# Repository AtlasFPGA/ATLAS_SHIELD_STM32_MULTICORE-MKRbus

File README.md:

# ATLAS_SHIELD_STM32_MULTICORE-MKRbus

Primera versión del SHIELD MULTICORE STM32 MKRbus para I/O BOARD ATLAS, válido para todas las "I/O BOARD ATLAS" incluidas las "AKA NEPTUNE" se usan las hembras apiladas que normalmente se usan en los shield de arduino, para tener el multicore basado en STM32.

Group ATLAS in Telegram: https://t.me/INICIATIVAATLAS

Enlace cabezales hembra apilable:
https://es.aliexpress.com/item/4000059515638.html?pdp_npi=2%40dis%21EUR%211%2C16%E2%82%AC%211%2C06%E2%82%AC%21%21%21%21%21%40211b440316861499958111903e1e40%2110000000140557195%21btf&_t=pvid%3Af4806f4c-de05-4d23-908d-d920b1f8ac6d&afTraceInfo=4000059515638__pc__pcBridgePPC__xxxxxx__1686149996&spm=a2g0o.ppclist.product.mainProduct&gatewayAdapt=glo2esp

Las STM32 que se han usado son 2 modelos para el presente diseño SHIELD MULTICORE STM32:
Los modelos escogidos son el mismo que se usa en Muticore-II/UnAMIGA, pero en la versión de Victor Trucco, con una sóla SD en modo de acceso SPI 3V3, el modelo de tener microcontroladores o SBCs en el futuro es válido para futuros SHIELD MULTICORE que puedan aparecer con esta interconexión, al incorporar de esta forma la unión FPGA-SD-MICRO FPGA-SD-SBC, estamos en un puro derivado de MiST.

De hecho con el tiempo Victor trucco ha ido agregando más funcionalidad MiST a su versión con bluepill.

En este caso he colocado el mismo diseño que se ha usado en máquinas retro-fpga como,Multicore-II, UnAMIGA, Prototipos PEGASO & CENTAURO, Y las Retrofpga de más capacidad UnAMIGA-Reloaded y NePTUNO, puede que con eL añadido de VGA64 muchos cores de poca profundidad de color sean portables.

Como reservé 2 pines para un modo 4bit en SD, este se puede desarrollar con la BLACKPILL en la opción del chip más avanzado F411.
Hay por ahora tres modelos de BLACKPILL la BLACKPILL que posée SDIO de 1Bit, 4Bit u 8Bits -> SDIO es el STM32F411CEU6.

## Pineado bluepill

bluepill -> stm32f103c8t6

## Pineado BLACKPILL

BLACKPILL -> STM32F411CEU6

Nota: para posicionar correctamente los pines usamos mayúsculas para la BLACKPILL, y minúsculas para la bluepill.

## Dimensiones que compraten las STM32 usadas, a tener en cuenta de la bluepill y la BLACKPILL:

Avance del esquema multicore STM32:

# NOTA: PI_TX y PI_RX pasarán as ser lineas de selección del modelo heredado por el Multicore II de Victor trucco.
# La colocación de los STM32, son excluyentes.

Al usar la elevación de las hembras apilables, el montaje "I/O BOARD ATLAS y LA SHIELD STM32" nos dá más capas, me queda la duda de si en el bus MKR+PMOD se puedieran cortar los pines asociados en la parte macho de las hembras apilables apoderándose de las señales Reservadas hasta la fecha, R14_SD_DATA2 y P14_SD_DATA1 así como el AUDIO Estéreo y T12_LEFT_MKR R11_RIGHT_MKR, agregando 4 señales a esta opción de Multicore con bluepill, estoy planteado en el futuro agregar esta opción de robar pines a la FPGA incorporando 4 señales a un nuevo diseño opcional, lo que permite conectar desde Dispositivos SPI, I2S, 2 canales I2C, TX RX con gestión de bflujo -> Acceso a internet.

Si se guardan los pines cortados iniciando el diseño con el bluepill y en el futuro se desarrollara una opción viable con SDIO 4Bit en BLACKPILL, no es muy dificil volver a soldarlos donde se realizó el corte, o directamente no usar ese tipo de hembras apilables en el conector de audio -> poner simples hembras, y hacer lo mismo en DATA1 y DATA2, y ya se veria como colocar pads normalmente abiertos o cerrados para que una misma placa permita obtener pines de fpga.

Aunque gestionando la compra de placas bien podía costearse una placa para bluepill + 4Señales, y BLACHPILL modelo F411.

Mi opción inicial es que se puedan manejar más componentes hardware, y unificar la placa sin agregar más que conectores cortar o soldar pistas en los pad indicados.

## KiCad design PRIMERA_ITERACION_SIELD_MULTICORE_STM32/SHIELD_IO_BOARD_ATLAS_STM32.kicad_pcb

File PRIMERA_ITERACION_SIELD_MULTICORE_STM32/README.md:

# Documentos del proyecto kicad asociado al SHIELD MULTICORE STM32
STM32 Multicore STM32 for plug a bluepill or BLACKPILL with CYC1000 in MKR bus for sxpand the use of Atlas resources

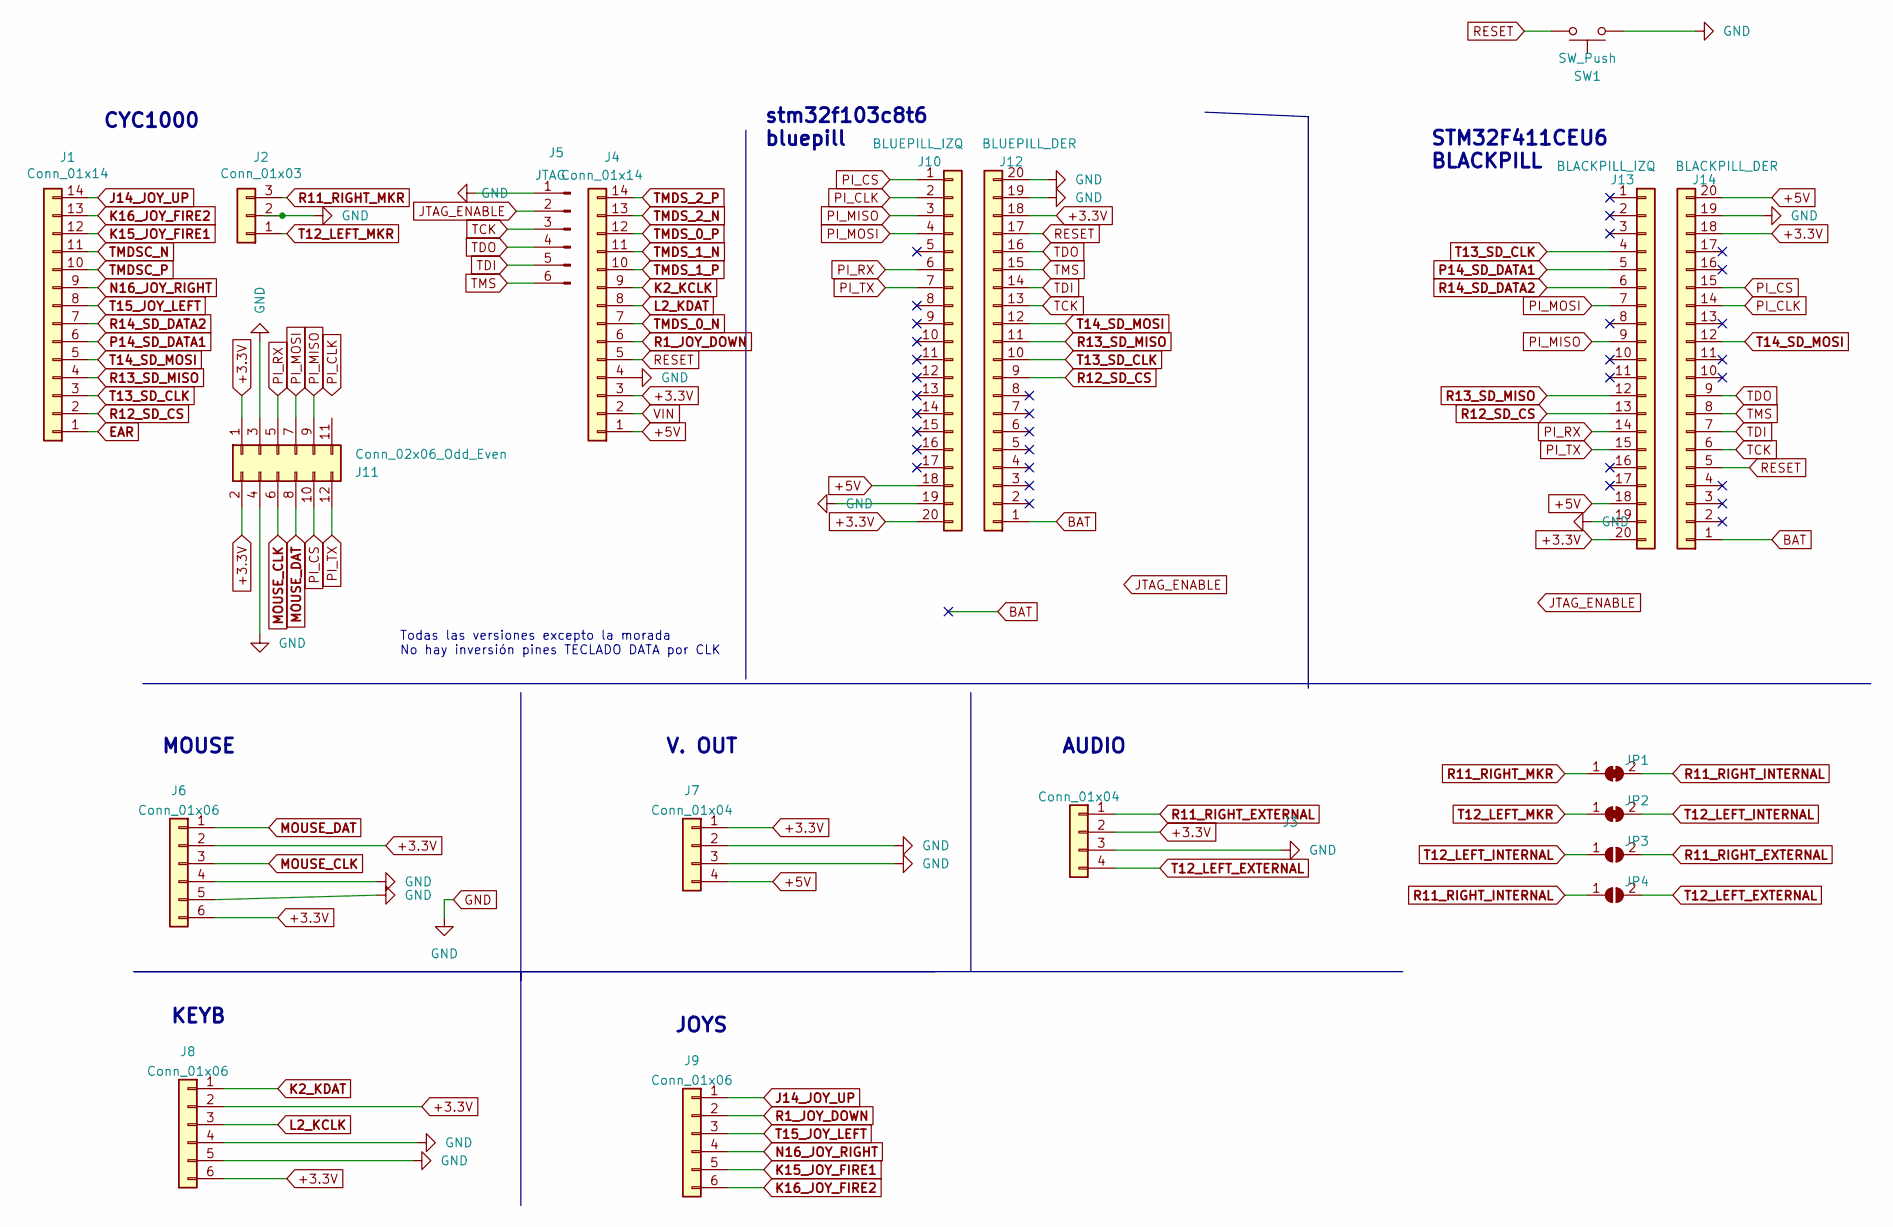
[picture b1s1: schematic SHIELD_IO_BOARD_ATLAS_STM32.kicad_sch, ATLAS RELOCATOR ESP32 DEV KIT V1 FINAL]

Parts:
J1, J4: Conn_01x14; PinHeader_1x14_P2.54mm_Vertical
J2: Conn_01x03; PinHeader_1x03_P2.54mm_Vertical
J3, J7: Conn_01x04; PinHeader_1x04_P2.54mm_Vertical
J5: JTAG; PinHeader_1x06_P2.54mm_Vertical
J6, J8, J9: Conn_01x06; PinHeader_1x06_P2.54mm_Vertical
J10: BLUEPILL_IZQ; PinHeader_1x20_P2.54mm_Vertical
J11: Conn_02x06_Odd_Even; PinHeader_2x06_P2.54mm_Vertical
J12: BLUEPILL_DER; PinHeader_1x20_P2.54mm_Vertical
J13: BLACKPILL_IZQ; PinHeader_1x20_P2.54mm_Vertical
J14: BLACKPILL_DER; PinHeader_1x20_P2.54mm_Vertical
JP1, JP2: SolderJumper_2_Bridged; SolderJumper-2_P1.3mm_Bridged2Bar_RoundedPad1.0x1.5mm
JP3, JP4: SolderJumper_2_Open; SolderJumper-2_P1.3mm_Open_RoundedPad1.0x1.5mm
SW1: SW_Push; SW_PUSH_6mm

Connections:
+3.3V: J3.2, J4.3, J6.2, J6.6, J7.1, J8.2, J8.6, J10.20, J11.1, J11.2, J12.18, J13.20, J14.18
+5V: J4.1, J7.4, J10.18, J13.18, J14.20
BAT: J12.1, J14.1
EAR: J1.1
GND: J2.2, J3.3, J4.4, J5.1, J6.4, J6.5, J7.2, J7.3, J8.4, J8.5, J10.19, J11.3, J11.4, J12.19, J12.20, J13.19, J14.19, SW1.2
J14_JOY_UP: J1.14, J9.1
JTAG_ENABLE: J5.2
K2_KCLK: J4.9
K2_KDAT: J8.1
K15_JOY_FIRE1: J1.12, J9.5
K16_JOY_FIRE2: J1.13, J9.6
L2_KCLK: J8.3
L2_KDAT: J4.8
MOUSE_CLK: J6.3, J11.6
MOUSE_DAT: J6.1, J11.8
N16_JOY_RIGHT: J1.9, J9.4
P14_SD_DATA1: J1.6, J13.5
PI_CLK: J10.2, J14.14
PI_CS: J10.1, J11.10, J14.15
PI_MISO: J10.3, J11.9, J13.9
PI_MOSI: J10.4, J11.7, J13.7
PI_RX: J10.6, J11.5, J13.14
PI_TX: J10.7, J11.12, J13.15
R1_JOY_DOWN: J4.6, J9.2
R11_RIGHT_EXTERNAL: J3.1, JP3.2 (B)
R11_RIGHT_INTERNAL: JP1.2 (B), JP4.1 (A)
R11_RIGHT_MKR: J2.3, JP1.1 (A)
R12_SD_CS: J1.2, J12.9, J13.13
R13_SD_MISO: J1.4, J12.11, J13.12
R14_SD_DATA2: J1.7, J13.6
RESET: J4.5, J12.17, J14.5, SW1.1
T12_LEFT_EXTERNAL: J3.4, JP4.2 (B)
T12_LEFT_INTERNAL: JP2.2 (B), JP3.1 (A)
T12_LEFT_MKR: J2.1, JP2.1 (A)
T13_SD_CLK: J1.3, J12.10, J13.4
T14_SD_MOSI: J1.5, J12.12, J14.12
T15_JOY_LEFT: J1.8, J9.3
TCK: J5.3, J12.13, J14.6
TDI: J5.5, J12.14, J14.7
TDO: J5.4, J12.16, J14.9
TMDSC_N: J1.11
TMDSC_P: J1.10
TMDS_0_N: J4.7
TMDS_0_P: J4.12
TMDS_1_N: J4.11
TMDS_1_P: J4.10
TMDS_2_N: J4.13
TMDS_2_P: J4.14
TMS: J5.6, J12.15, J14.8
VIN: J4.2

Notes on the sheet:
MOUSE
CYC1000
AUDIO
KEYB
JOYS
stm32f103c8t6 bluepill
Todas las versiones excepto la morada No hay inversión pines TECLADO DATA por CLK
STM32F411CEU6 BLACKPILL
V. OUT

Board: 2 copper layers, 19 parts (8 on the bottom side), 35 nets, no tracks yet.

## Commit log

2023-06-07 PRIMER README.md
    Multicore válido para BLACKPILL y BLUEPILL.
2023-06-07 Información Bluepill y blackpill
2023-06-07 Create Aclaración
    Inicio del proyecto en KICAD para el Multicore Shield STM32
2023-06-07 AÑADIDOS FICHEROS DE KICAD, MODELO UNA ÚNICA SD PARA ATLAS
2023-06-07 Imágenes de los STM32 usados, README.md
2023-06-07 Esquema común para desarrollo de un multicore STM32
    BLACKPILL -> SIO 4BIT
    bluepill -> SPI
2023-06-07 Agregada imagen del Diagrama multicore para bluepill y BLACKPILL README.md
2023-06-07 Añadir foto de Hembras apilables
2023-06-07 Agregar información sobre donde comprar las hembras apilables README.md
2023-06-07 Añadir información sobre el cambio RX y TX Update README.md
    Las señales PI_RX y PI_TX pasarán a ser señales de selección, las mismas que usa Victor Trucco en su Multicore II.
2023-06-07 Primera_versión_del_multicore_stm32
2023-06-07 Agregada información sobre la placa SHIELD MULTICORE STM32 Update README.md
2023-06-07 Añadir información sobre capturar señales usando cabezales hembra
2023-06-07 Añadir infomación sobre hembras apilables
    Aclaración en texto a proceder en el futuro si se mezclan hembras con hembras apilables, si se desea usar un bluepill con 4 pines extra, o en el futuro un BLACKPILL F411 para desarrollar SDIO 4BIT.
2023-06-07 Aclarar futura opción PADs para agregar señales a bluepill-MiST
2023-06-07 Hablar de las señales capturadas en caso de usar BLUEPILL
2023-06-07 Mejorar redacción captura de pines al usar bluepill
2023-06-08 Agregar documentación al readme dell fichero alojado en el proyecto de KiCAD.
2023-12-11 Update README.md
    Group ATLAS in Telegram: https://t.me/INICIATIVAATLAS

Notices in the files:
PRIMERA_ITERACION_SIELD_MULTICORE_STM32/SHIELD_IO_BOARD_ATLAS_STM32.kicad_pcb:
Licensed under Cern OHL http://ohwr.org/cernohl
